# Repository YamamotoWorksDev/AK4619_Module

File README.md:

# AK4619 Module
This is a module board for prototyping digital synthesizers or mixers, featuring a 4-channel audio codec (AK4619VN) that supports up to 192 kHz.

## How to buy
### 2x2
- [Tindie(International)](https://www.tindie.com/products/yamamotoworks/ak4619vn-codec-module-2x2/)  
- [BASE(Japan)](https://miyworks.base.shop/items/131805475)

### 1x4
- [Tindie(International)](https://www.tindie.com/products/yamamotoworks/ak4619vn-codec-module-1x4/)  
- [BASE(Japan)](https://miyworks.base.shop/items/139583333)

## Specifications
- Power: 5V input, onboard 3.3V regulator (AP7361)
- CODEC IC: [AK4619VN](https://www.akm.com/global/en/products/audio/audio-codec/ak4619vn/)
  - Channels: 4in/4out
  - Sample Rate: 192kHz(max.)
  - TDM Slave (expects external BCLK/LRCLK and MCLK)
- Audio Jack: [Green Thonkiconn Stereo 3.5mm Jack Socket](https://www.thonk.co.uk/shop/thonkiconn/)
- RESET IC: [ADM811](https://www.analog.com/en/products/adm811.html)
- Power IC: [AP7361EA-33E-13](https://www.diodes.com/assets/Datasheets/AP7361EA.pdf)

## Codec Initialization(Example)
```c
void AUDIO_Init_AK4619(uint32_t hz)
{
    uint8_t sndData[1] = {0x00};

    // AK4619 HW Reset
    HAL_GPIO_WritePin(CODEC_RESET_GPIO_Port, CODEC_RESET_Pin, 0);
    HAL_Delay(10);
    HAL_GPIO_WritePin(CODEC_RESET_GPIO_Port, CODEC_RESET_Pin, 1);
    HAL_Delay(500);

    // Audio I/F format
    sndData[0] = 0xAC;  // 1 010 11 00 (TDM, 32bit, TDM128 I2S compatible, Falling, Slow)
    HAL_I2C_Mem_Write(&hi2c3, (0b0010001 << 1), 0x01, I2C_MEMADD_SIZE_8BIT, sndData, sizeof(sndData), 10000);

    // Reset Control
    sndData[0] = 0x10;  // 000 1 00 00
    HAL_I2C_Mem_Write(&hi2c3, (0b0010001 << 1), 0x02, I2C_MEMADD_SIZE_8BIT, sndData, sizeof(sndData), 10000);

    // System Clock Setting (example: 96kHz)
    sndData[0] = 0x01;  // 00000 001 (96kHz)
    HAL_I2C_Mem_Write(&hi2c3, (0b0010001 << 1), 0x03, I2C_MEMADD_SIZE_8BIT, sndData, sizeof(sndData), 10000);

    // ADC Input Setting
    sndData[0] = 0x55;  // 01 01 01 01 (AIN1L, AIN1R, AIN4L, AIN4R)
    HAL_I2C_Mem_Write(&hi2c3, (0b0010001 << 1), 0x0B, I2C_MEMADD_SIZE_8BIT, sndData, sizeof(sndData), 10000);

    // DAC Input Select Setting
    // sndData[0] = 0x0E;  // 00 00 11 10 (ADC1 -> DAC1, ADC2 -> DAC2)
    sndData[0] = 0x04;  // 00 00 01 00 (SDIN2 -> DAC2, SDIN1 -> DAC1)
    HAL_I2C_Mem_Write(&hi2c3, (0b0010001 << 1), 0x12, I2C_MEMADD_SIZE_8BIT, sndData, sizeof(sndData), 10000);

    // Power Management
    sndData[0] = 0x37;  // 00 11 0 11 1
    HAL_I2C_Mem_Write(&hi2c3, (0b0010001 << 1), 0x00, I2C_MEMADD_SIZE_8BIT, sndData, sizeof(sndData), 10000);
}
```

## Application Example
- [JUMBLEQ](https://github.com/yamamo2shun1/JUMBLEQ)

## Size
### 2x2

### 1x4

## Photos
### 2x2

### 1x4

## License
The hardware design files in this repository are licensed under the
**CERN Open Hardware Licence Version 2 - Permissive (CERN-OHL-P-2.0)**.

Unless otherwise stated, the following are treated as hardware design files covered by CERN-OHL-P-2.0:

- KiCad schematic files
- PCB layout files

A copy of the license text is provided in the `LICENSE` file.

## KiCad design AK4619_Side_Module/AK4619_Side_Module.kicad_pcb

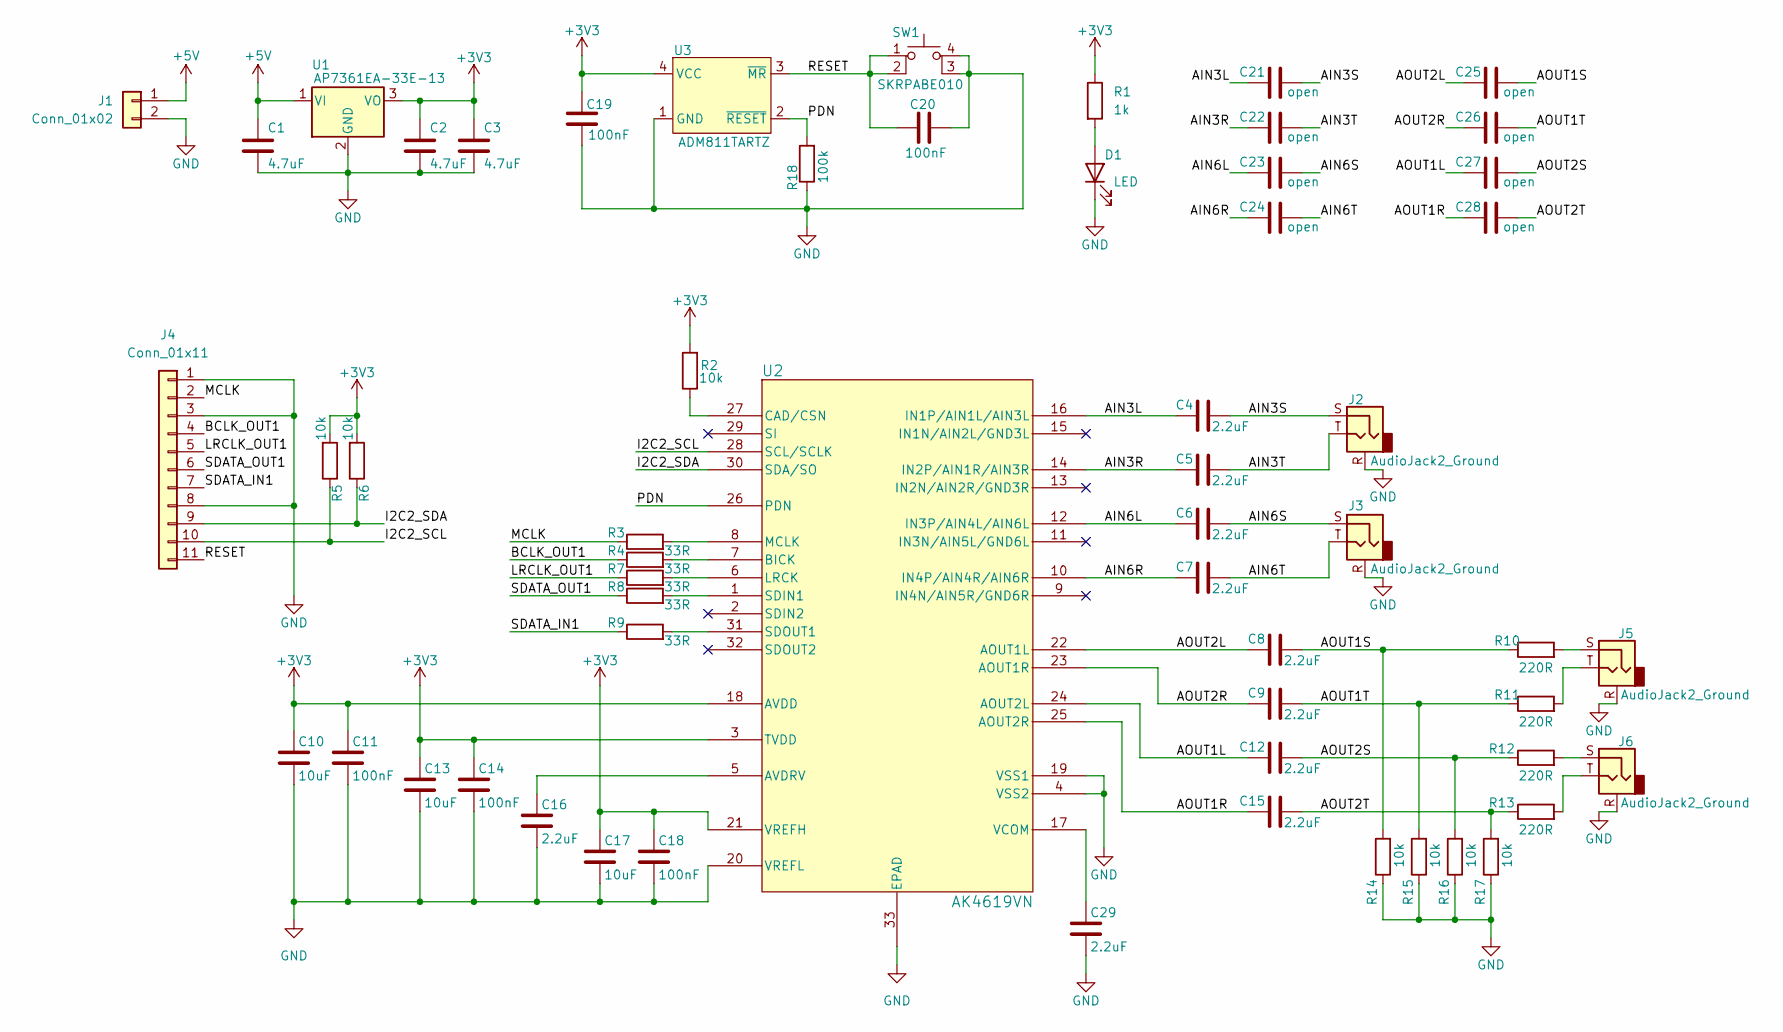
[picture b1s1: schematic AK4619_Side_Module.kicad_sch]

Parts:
C1, C2, C3: 4.7uF; C_0603_1608Metric
C4, C5, C6, C7, C8, C9, C12, C15: 2.2uF; C_1210_3225Metric_Pad1.33x2.70mm_HandSolder
C10, C13, C17: 10uF; C_0402_1005Metric
C11, C14, C18: 100nF; C_0201_0603Metric
C16, C29: 2.2uF; C_0201_0603Metric
C19, C20: 100nF; C_0402_1005Metric
C21, C22, C23, C24, C25, C26, C27, C28: open; C_1812_4532Metric_Pad1.57x3.40mm_HandSolder
D1: LED; LED_0603_1608Metric
J1: Conn_01x02; JST_PH_B2B-PH-K_1x02_P2.00mm_Vertical
J2, J3, J5, J6: AudioJack2_Ground; Jack_3.5mm_QingPu_WQP-PJ366ST_Vertical
J4: Conn_01x11; PinSocket_1x11_P2.54mm_Vertical
R1: 1k; R_0201_0603Metric
R2, R5, R6: 10k; R_0201_0603Metric
R3, R4, R7, R8, R9: 33R; R_0201_0603Metric
R10, R11, R12, R13: 220R; R_0603_1608Metric_Pad0.98x0.95mm_HandSolder
R14, R15, R16, R17: 10k; R_0201_0603Metric_Pad0.64x0.40mm_HandSolder
R18: 100k; R_0201_0603Metric
SW1: SKRPABE010
U1: AP7361EA-33E-13; SOT-223-3_TabPin2
U2: AK4619VN; AK4619VN_AKM
U3: ADM811TARTZ; SOT-143

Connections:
+3V3: C2.1, C3.1, C10.1, C11.1, C13.1, C14.1, C17.1, C18.1, C19.1, R1.1, R2.2, R5.2, R6.2, U1.3 (VO), U2.3 (TVDD), U2.18 (AVDD), U2.21 (VREFH), U3.4 (VCC)
+5V: C1.1, J1.1, U1.1 (VI)
/AIN3L: C4.1, C21.1, U2.16 (IN1P/AIN1L/AIN3L)
/AIN3R: C5.1, C22.1, U2.14 (IN2P/AIN1R/AIN3R)
/AIN3S: C4.2, C21.2, J2.S
/AIN3T: C5.2, C22.2, J2.T
/AIN6L: C6.1, C23.1, U2.12 (IN3P/AIN4L/AIN6L)
/AIN6R: C7.1, C24.1, U2.10 (IN4P/AIN4R/AIN6R)
/AIN6S: C6.2, C23.2, J3.S
/AIN6T: C7.2, C24.2, J3.T
/AOUT1L: C12.1, C27.1, U2.24 (AOUT2L)
/AOUT1R: C15.1, C28.1, U2.25 (AOUT2R)
/AOUT1S: C8.2, C25.2, R10.1, R14.2
/AOUT1T: C9.2, C26.2, R11.1, R15.2
/AOUT2L: C8.1, C25.1, U2.22 (AOUT1L)
/AOUT2R: C9.1, C26.1, U2.23 (AOUT1R)
/AOUT2S: C12.2, C27.2, R12.1, R16.2
/AOUT2T: C15.2, C28.2, R13.1, R17.2
/BCLK_OUT1: J4.4, R4.1
/I2C2_SCL: J4.10, R5.1, U2.28 (SCL/SCLK)
/I2C2_SDA: J4.9, R6.1, U2.30 (SDA/SO)
/LRCLK_OUT1: J4.5, R7.1
/MCLK: J4.2, R3.1
/PDN: R18.2, U2.26 (PDN), U3.2 (~RESET)
/RESET: C20.1, J4.11, SW1.1, SW1.2, U3.3 (~MR)
/SDATA_IN1: J4.7, R9.1
/SDATA_OUT1: J4.6, R8.1
GND: C1.2, C2.2, C3.2, C10.2, C11.2, C13.2, C14.2, C16.2, C17.2, C18.2, C19.2, C20.2, C29.2, D1.1 (K), J1.2, J2.R, J3.R, J4.1, J4.3, J4.8, J5.R, J6.R, R14.1, R15.1, R16.1, R17.1, R18.1, SW1.3 (K), SW1.4 (A), U1.2 (GND), U2.4 (VSS2), U2.19 (VSS1), U2.20 (VREFL), U2.33 (EPAD), U3.1 (GND)
unnamed: D1.2 (A), R1.2
unnamed: J5.S, R10.2
unnamed: J5.T, R11.2
unnamed: J6.S, R12.2
unnamed: J6.T, R13.2
unnamed: C16.1, U2.5 (AVDRV)
unnamed: R4.2, U2.7 (BICK)
unnamed: R2.1, U2.27 (CAD/CSN)
unnamed: R7.2, U2.6 (LRCK)
unnamed: R3.2, U2.8 (MCLK)
unnamed: R8.2, U2.1 (SDIN1)
unnamed: R9.2, U2.31 (SDOUT1)
unnamed: C29.1, U2.17 (VCOM)

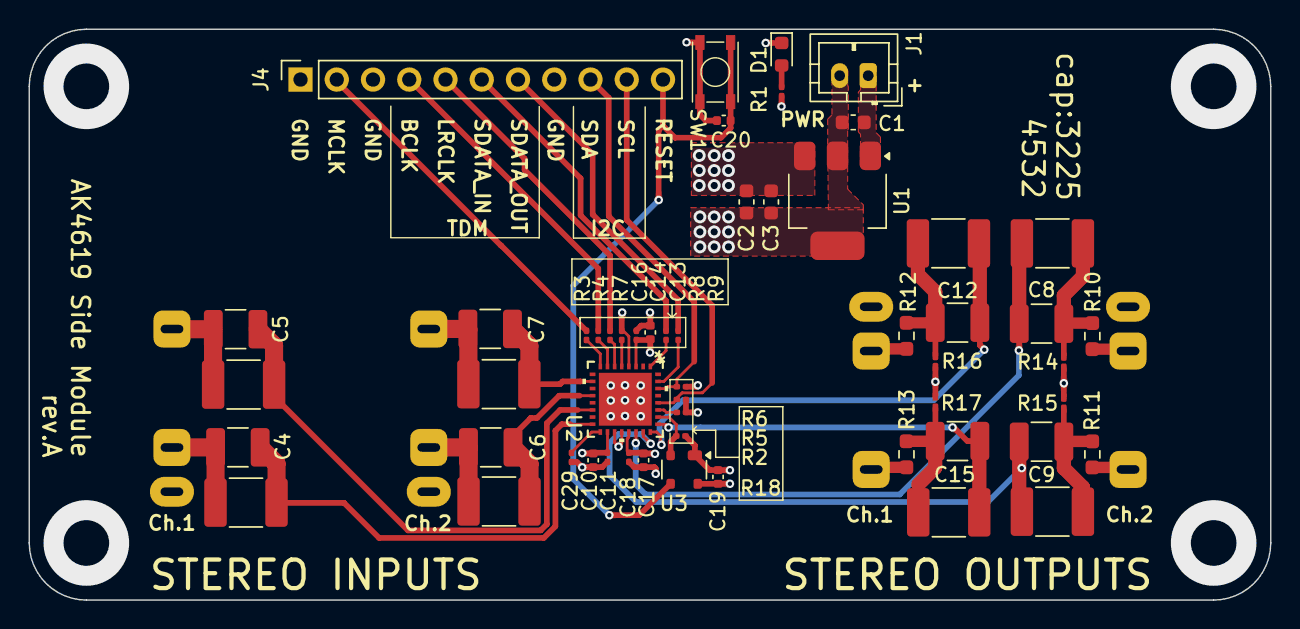
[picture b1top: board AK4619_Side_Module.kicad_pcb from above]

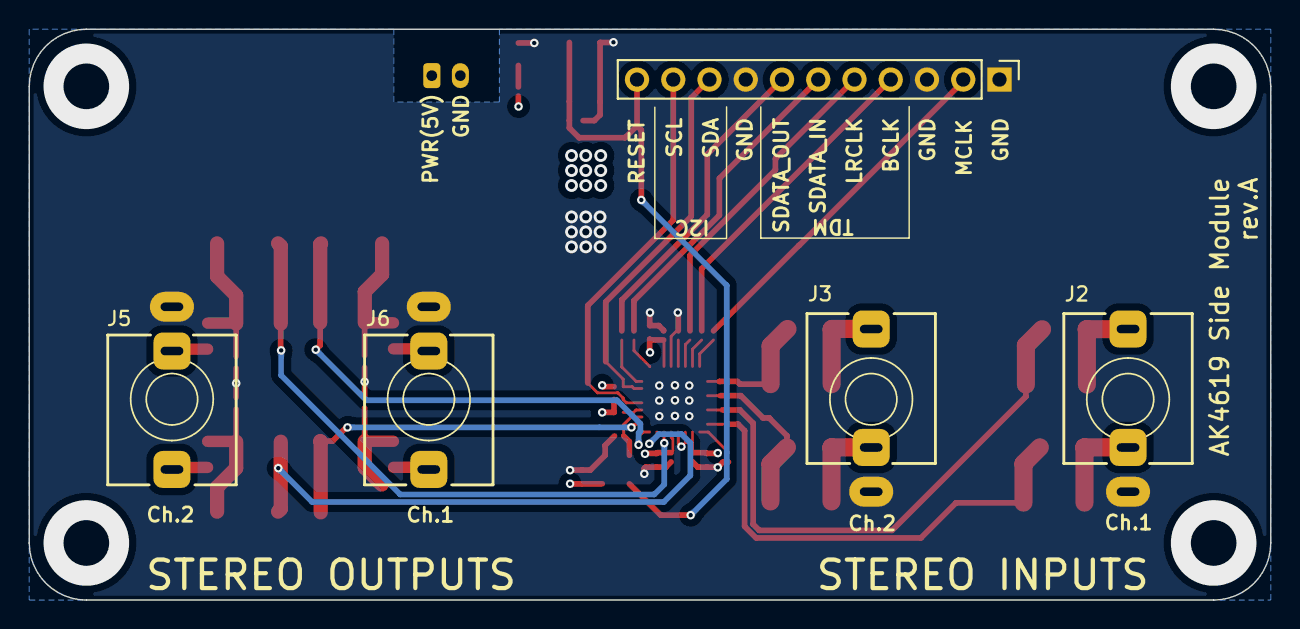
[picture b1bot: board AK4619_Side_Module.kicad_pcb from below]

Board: 4 copper layers, 87.0 x 40.0 mm, 58 parts (4 on the bottom side), 41 nets.

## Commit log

2026-01-13 Enhance README with specifications and images
    Updated the README to provide detailed specifications and photos of the AK4619 module.
2026-01-13 Add ignore file.
2026-01-13 Add Kicad project files.
2026-01-13 Add schematic.
2026-01-13 Add codec initialization example to README
    Added example code for codec initialization.
2026-01-13 Fix typo in Audio Jack description
2026-01-14 C4,5,6,7,8,9,12,15の値を修正
2026-03-08 Add license section to README
    Added license information for hardware design files.
2026-03-08 Changed license from MIT to CERN-OHL-P 2.0
2026-03-08 Update license file reference in README
2026-03-08 Renewed
2026-03-09 Add buying instructions to README
    Added purchasing information for the audio module.
2026-03-10 Enhance README description of AK4619 module
    Updated the description of the AK4619 module to provide more details about its features.
2026-03-10 Revise README for AK4619 Module details
    Updated module name and improved specifications formatting.
2026-03-10 Modify the silk in the Bottom Layer
2026-03-11 Add Kicad projects(side panel version)
2026-03-11 Add dimension annotations to the PCB data.
2026-03-12 Change the 3D model data path settings.
2026-03-25 Add images for 2x2 and 1x4 sections in README
    Added photos for 2x2 and 1x4 configurations to README.
2026-03-25 Update image link for DSCF7968 in README
2026-03-25 Revise image captions for 2x2 and 1x4 sections
    Updated image captions for clarity in the README.
2026-03-25 Add purchasing options for 2x2 and 1x4 configurations
2026-03-25 Add size section with example images to README
    Added size examples with images for 2x2 and 1x4 configurations.
2026-03-25 Replace 1x4 images in README
    Updated images for 1x4 section in README.
2026-03-25 Update purchase links for AK4619VN codec module
2026-04-15 Update images in README for size sections
2026-04-15 Clean up symbol placement
2026-04-15 Add dimension annotations
2026-04-15 Renew
